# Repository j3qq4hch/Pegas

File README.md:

# Материнская плата БПЛА Pegas

Данный репозиторий содержит документацию и исходные файлы печатных плат электроники БПЛА Пегас.
Набортная электроника представляет собой главным образом материнскую плату (одну или набор из двух), которая служит для распределения питания внутри дрона, а также предоставляет интерфейс для подключения внешних устройств к автопилоту (удобные в производстве и использовании разъемы в удобных местах). БПЛА Пегас использует PX4-совместимый автопилот Cube Orange, которому всегда требуется некая материнская плата (carrier board в репозитории самого автопилота), т.к. он подключается ко всем внешним устройствам разъемом Hirose DF17(1.0H)-80DP-0.5V(57).

Было спроектировано несколько итераций электроники БПЛА Пегас.
## V1 
Самая первая версия устройства, состоящая из одной четырехслойной печатной платы.
Было произведен только один прототип, после чего была спроектирована следующая версия.

## V2
Минимальные отличия от V1, в частности: иная ориентация Cube Orange на плате (он повернут на 60 градусов), что было вызвано багом с устновлением нулевого положения встроенного компаса в ПО PX4, также добавлена схема выключения устройства на N-канальных полевых транзисторах. Схема выключения в этой версии неработоспособна и никогда не была исправлена. 

Также эта версия может быть дополнена внешним ethernet-роутером, который монтируется внутри фюзеляжа БПЛА на специальном кронштейне.

Было спроектировано две платы переходника для покупных модулей роутеров:

Было произведено несколько плат (до 10), которые используются в первых коммерческих аппаратах.

## V3
Полностью переработанная версия электроники: одна четырехслойная материнская плата  заменена на две двухслойные, соединенные мезонинным способом. Снизу располагается силовая плата, на которой размещаются разъемы для подключения моторов, медные полигоны распреления силового питания, DC-DC преобразователи всех вторичных линий питания, а также схема выключения на N-канальных полевых транзисторах. Сверху располагается плата логики с автопилотом и всеми разъемами для подключения внешних устройств. В этой версии произошел переход с миниатюрных разъемов серии JST-GH (как в UAVCAN) на несколько более крупные и значительно более удобные и надежные разъемы JST-XA с защелкой. 

Этот вариант материнской платы предназначен для сборки СЫЧ-версии Пегаса, поэтому помимо типичных компонентов на плате логики также располагается располагается покупной модуль ethernet-концентратора (ссылка тут) и модем телеметрии, поставляемый заказчиком (картинка тут).

Эта версия электроники никогда не была произведена и послужила основой для версии 3.1.

## V3.1

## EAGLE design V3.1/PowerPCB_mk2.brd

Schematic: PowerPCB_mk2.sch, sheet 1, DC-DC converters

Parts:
C1, C10, C16, C25, C39, C58: 0.1u; C0603; VOLTAGE 50V; LCSC# C14663
C2, C3, C4, C11, C12, C13, C17, C18, C19, C26, C27, C33, C44, C54: 2.2u; C1206; VOLTAGE 100V; LCSC# C170101
C5, C14, C20, C34, C45, C62, C88: 4700p; C0603; VOLTAGE 50V; LCSC# C106218
C6, C15, C21, C35, C87: 47p; C0603; VOLTAGE 50V; LCSC# C1671
C7, C8, C9, C22, C23, C24, C36, C37, C38, C43, C56, C57: 47u; C1206; VOLTAGE 25V; LCSC# C403725
C28, C29, C30, C31, C32, C42: 10u; C1210; VOLTAGE 50V; LCSC# C77102
C40, C41: DNP; C0603
CON1: PINHEAD_1X12-2.54-FEMALE; 1X12-PTH-2.54-FEMALE
CON2, CON4, CON7: PINHEAD_1X06-2.54-FEMALE; 1X06-PTH-2.54-FEMALE
CON3: PINHEAD_1X02-2.54-FEMALE; 1X02-PTH-2.54-FEMALE
D1, D2, D3, D4, D10: B560C; DO-214AB(SMC)
IC1, IC2, IC3, IC4: TPS54560B; SOIC8-POWERPAD
IC5: INA169; SOT23-5
IC10: TPS54260; MSOP10; DIGIKEY# 296-28183-1-ND
J1: CONNECTION-7MM; CONNECTION_7MM
L1: 3.3uH; IHLP-2020BZ-01; LCSC# C844988
L2, L4, L5: 7.2uH; 1064
L3: 22µH; SRP1265A
Q1: IRLML9301; SOT23
R1, R5, R9, R13: 243K; R0603; LCSC# C23351
R2, R6, R10, R14, R22, R29: 18K; R0603; LCSC# C25810
R3, R11: 53K6; R0603; LCSC# C23074
R4, R8, R12, R16, R17, R20, R23, R28: 10K; R0603; LCSC# C160601
R7, R15, R21, R25: 143K; R0603; LCSC# C22877
R18, R26: 700 µOhms; R3920-KELVIN
R27: 39K; R0603; LCSC# C23153
RL: 53K6; R0603; LCSC# C23074
RL1: DNM; R0603; LCSC# C23153

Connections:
5VFMU: C7.P$2 (2), C8.P$2 (2), C9.P$2 (2), C39.2, IC5.5 (V+), L2.2, Q1.2 (S), R3.2, R23.1; also elsewhere on the board
5V_FMU_CTRL: Q1.1 (G), R23.2
BATNEG: CON3.1
BATT_CURRENT: C40.2, CON1.12, IC5.1 (OUT), RL.2, RL1.2
BATT_VOLTAGE: C41.2, CON1.11, R20.2, R22.1
BOOT: C58.2, IC10.1 (BOOT)
BOOT1: C1.1, IC1.1 (BOOT)
BOOT2: C16.1, IC3.1 (BOOT)
BOOT3: C25.1, IC4.1 (BOOT)
DC-DC_EN: IC2.3 (EN), IC3.3 (EN), IC4.3 (EN), IC10.3 (EN); also elsewhere on the board
GND: C2.P$1 (1), C3.P$1 (1), C4.P$1 (1), C5.1, C6.1, C7.P$1 (1), C8.P$1 (1), C9.P$1 (1), C11.P$1 (1), C12.P$1 (1), C13.P$1 (1), C14.1, C15.1, C17.P$1 (1), C18.P$1 (1), C19.P$1 (1), C20.1, C21.1, C22.P$1 (1), C23.P$1 (1), C24.P$1 (1), C26.P$1 (1), C27.P$1 (1), C28.1, C29.1, C30.1, C31.1, C32.1, C33.P$1 (1), C34.1, C35.1, C36.P$1 (1), C37.P$1 (1), C38.P$1 (1), C39.1, C40.1, C41.1, C42.1, C43.P$2 (2), C44.P$1 (1), C45.2, C54.P$1 (1), C56.P$2 (2), C57.P$2 (2), C62.2, C87.2, C88.2, CON1.1, CON1.2, CON1.5, CON1.6, CON1.7, CON2.1, CON2.2, CON2.3, CON4.4, CON4.5, CON4.6, CON7.4, CON7.5, CON7.6, D1.A, D2.A, D3.A, D4.A, D10.A, IC1.7 (GND), IC1.P$1 (GND), IC2.7 (GND), IC2.P$1 (GND), IC3.7 (GND), IC3.P$1 (GND), IC4.7 (GND), IC4.P$1 (GND), IC5.2 (GND), IC10.9 (GND), IC10.EP (GND), J1.2, R1.1, R4.1, R5.1, R8.1, R9.1, R12.1, R13.1, R16.1, R17.1, R20.1, R25.1, R28.1, RL.1, RL1.1; also elsewhere on the board
unnamed: IC1.4 (RT/CLK), R1.2
unnamed: IC3.4 (RT/CLK), R9.2
unnamed: C6.2, IC1.6 (COMP), R2.2
unnamed: C5.2, R2.1
unnamed: IC1.5 (FB), R3.1, R4.2
unnamed: C21.2, IC3.6 (COMP), R10.2
unnamed: C10.1, IC2.1 (BOOT)
unnamed: C10.2, D2.C, IC2.8 (SW), L3.1
unnamed: IC2.4 (RT/CLK), R5.2
unnamed: C15.2, IC2.6 (COMP), R6.2
unnamed: C14.2, R6.1
unnamed: IC2.5 (FB), R7.1, R8.2, R17.2
unnamed: C20.2, R10.1
unnamed: IC4.4 (RT/CLK), R13.2
unnamed: IC3.5 (FB), R11.1, R12.2
unnamed: C35.2, IC4.6 (COMP), R14.2
unnamed: C34.2, R14.1
unnamed: IC4.5 (FB), R15.1, R16.2
unnamed: IC5.4 (VIN-), R18.S2, R26.S2
unnamed: C45.1, C62.1, IC10.4 (SS/TR)
unnamed: IC5.3 (VIN+), R18.S1, R26.S1
unnamed: R21.1, R22.2
unnamed: CON1.8, CON1.9, CON1.10, Q1.3 (D)
unnamed: C87.1, IC10.8 (COMP), R29.2
unnamed: IC10.5 (RT/CLK), R25.2
unnamed: C88.1, R29.1
PGND: J1.1; also elsewhere on the board
PH: C58.1, D10.C, IC10.10 (PH), L1.P$1 (1)
PWRSW: CON3.2
SW1: C1.2, D1.C, IC1.8 (SW), L2.1
SW2: C16.2, D3.C, IC3.8 (SW), L4.1
SW3: C25.2, D4.C, IC4.8 (SW), L5.1
VBAT: C2.P$2 (2), C3.P$2 (2), C4.P$2 (2), C11.P$2 (2), C12.P$2 (2), C13.P$2 (2), C17.P$2 (2), C18.P$2 (2), C19.P$2 (2), C26.P$2 (2), C27.P$2 (2), C33.P$2 (2), C44.P$2 (2), C54.P$2 (2), IC1.2 (VIN), IC2.2 (VIN), IC3.2 (VIN), IC4.2 (VIN), IC10.2 (VIN), R18.2, R18.22 (2), R21.2, R26.2, R26.22 (2); also elsewhere on the board
VDC: R18.1, R18.11 (1), R26.1, R26.11 (1); also elsewhere on the board
VDD_4V: C43.P$1 (1), C56.P$1 (1), C57.P$1 (1), CON1.3, CON1.4, L1.P$2 (2), R27.2
VDD_5V: C22.P$2 (2), C23.P$2 (2), C24.P$2 (2), CON4.1, CON4.2, CON4.3, L4.2, R11.2
VDD_12V: C36.P$2 (2), C37.P$2 (2), C38.P$2 (2), CON7.1, CON7.2, CON7.3, L5.2, R15.2
VDD_24V: C28.2, C29.2, C30.2, C31.2, C32.2, C42.2, CON2.4, CON2.5, CON2.6, L3.2, R7.2
VSENSE: IC10.7 (VSENSE), R27.1, R28.2

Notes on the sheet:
24V power source
5V power source
When EN is left floating TPS54560 is enabled
12V power source
EN - Enable terminal, with internal pull-up current source. Pull below 1.2 V to disable. Float to enable.
EN PIN: Pull below 1.2 V to disable. Float to enable.
143K on RT/CLK is for ~800 KHz switching frequency
TPS54560/54260 Vout = 0.8 * (Rh/Rl + 1)
Vout = 3,92 V
Vout = 23,68 V
Vout = 12,24 V
Vout = 5.088
Place C3 in case low pass filtering on the output needed
For most applications, best performance is attained with an RS value that provides a full-scale shunt voltage of 50 mV to 100 mV; maximum input voltage for accurate measurements is 500 mV.
Imax = 169 A Vout max = 3.17 V

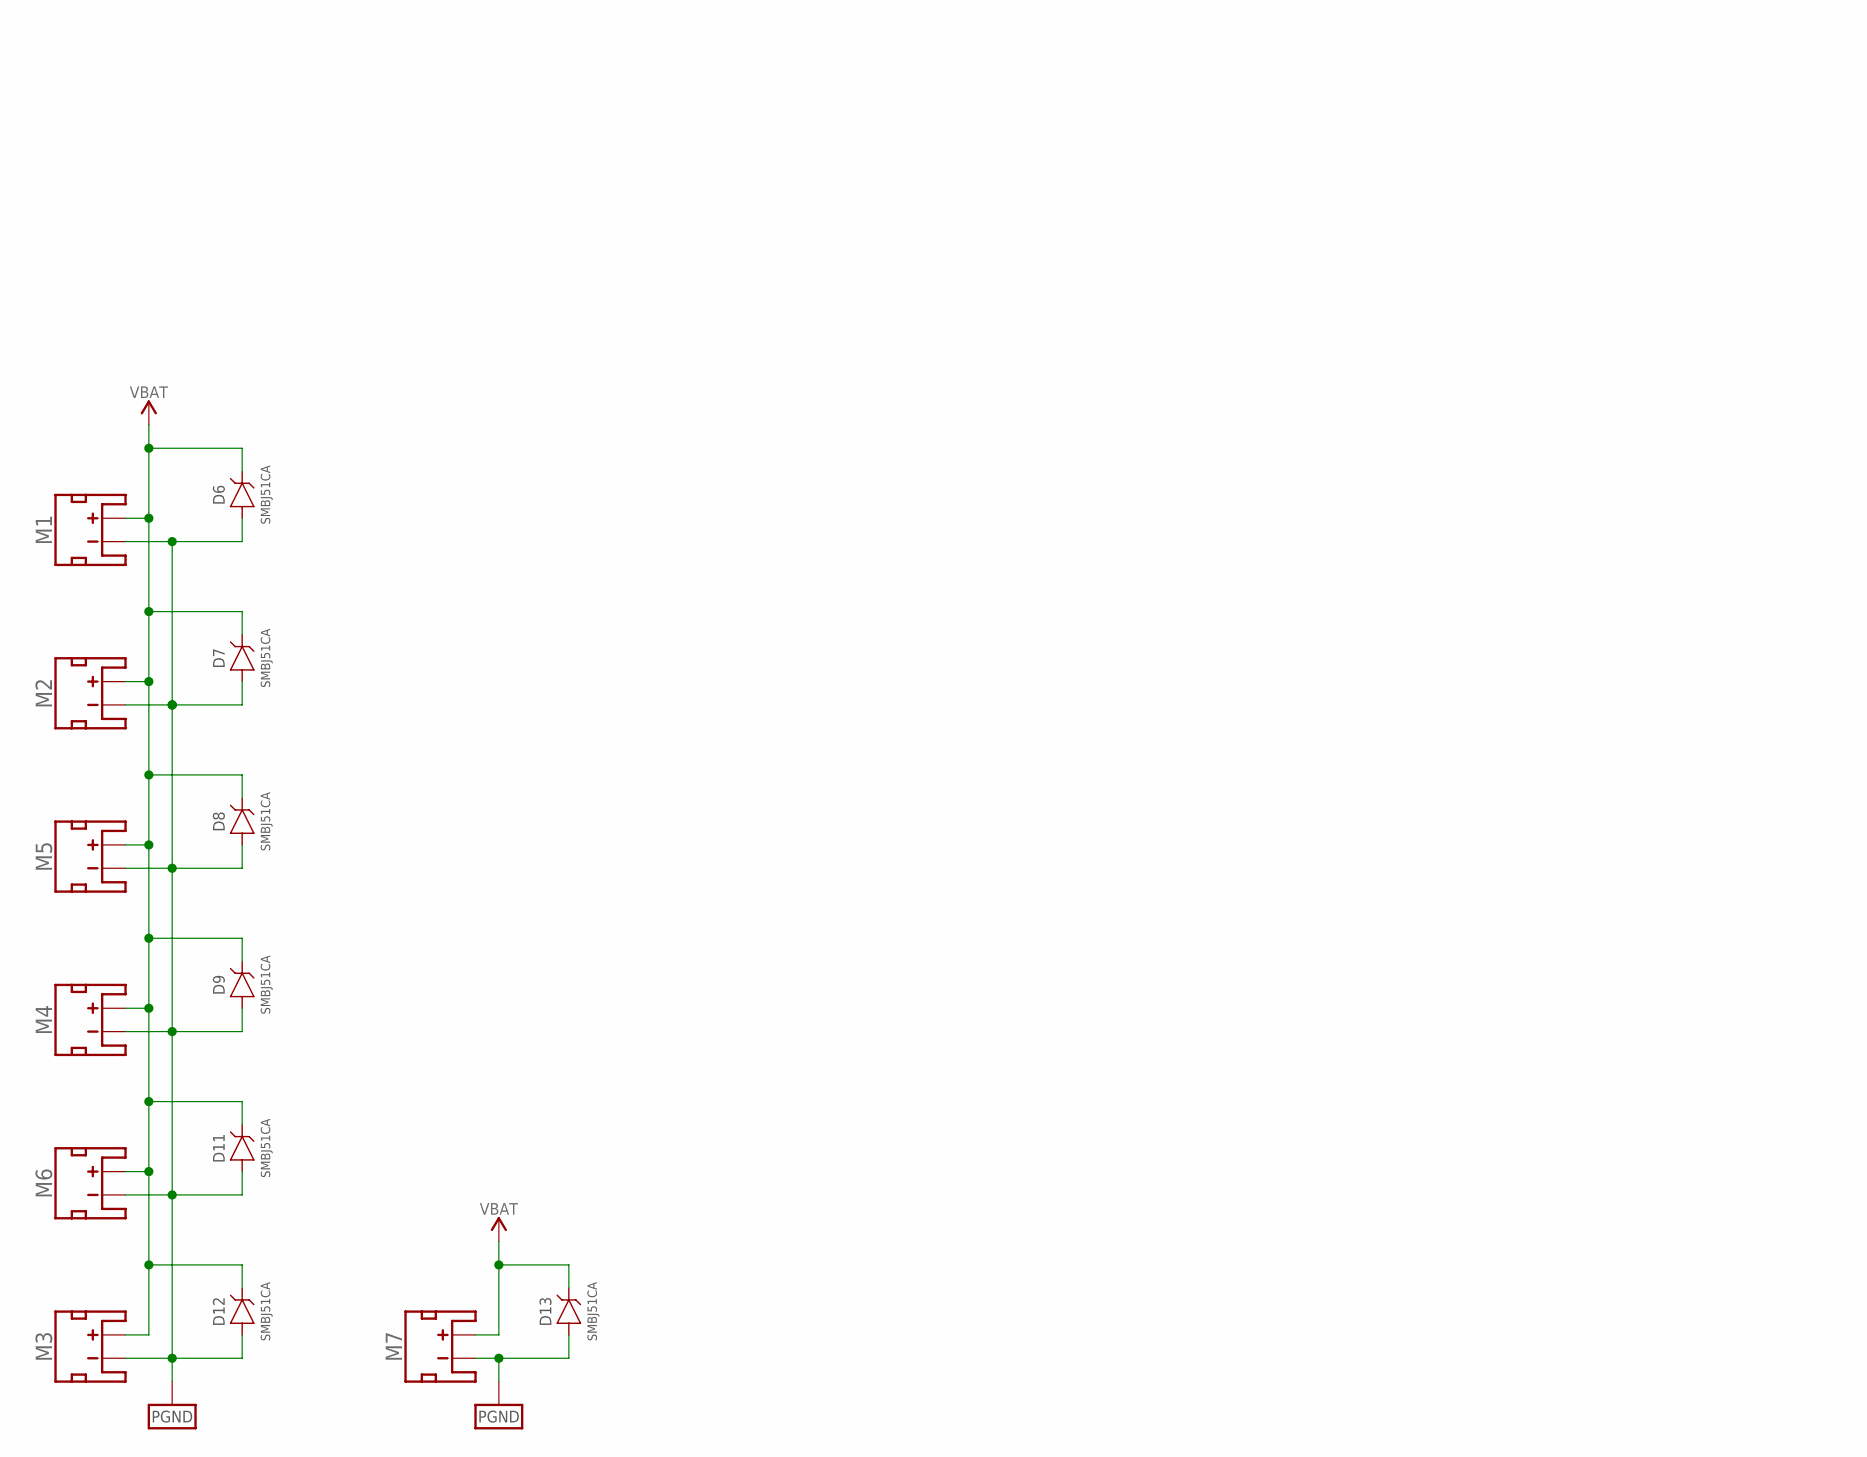
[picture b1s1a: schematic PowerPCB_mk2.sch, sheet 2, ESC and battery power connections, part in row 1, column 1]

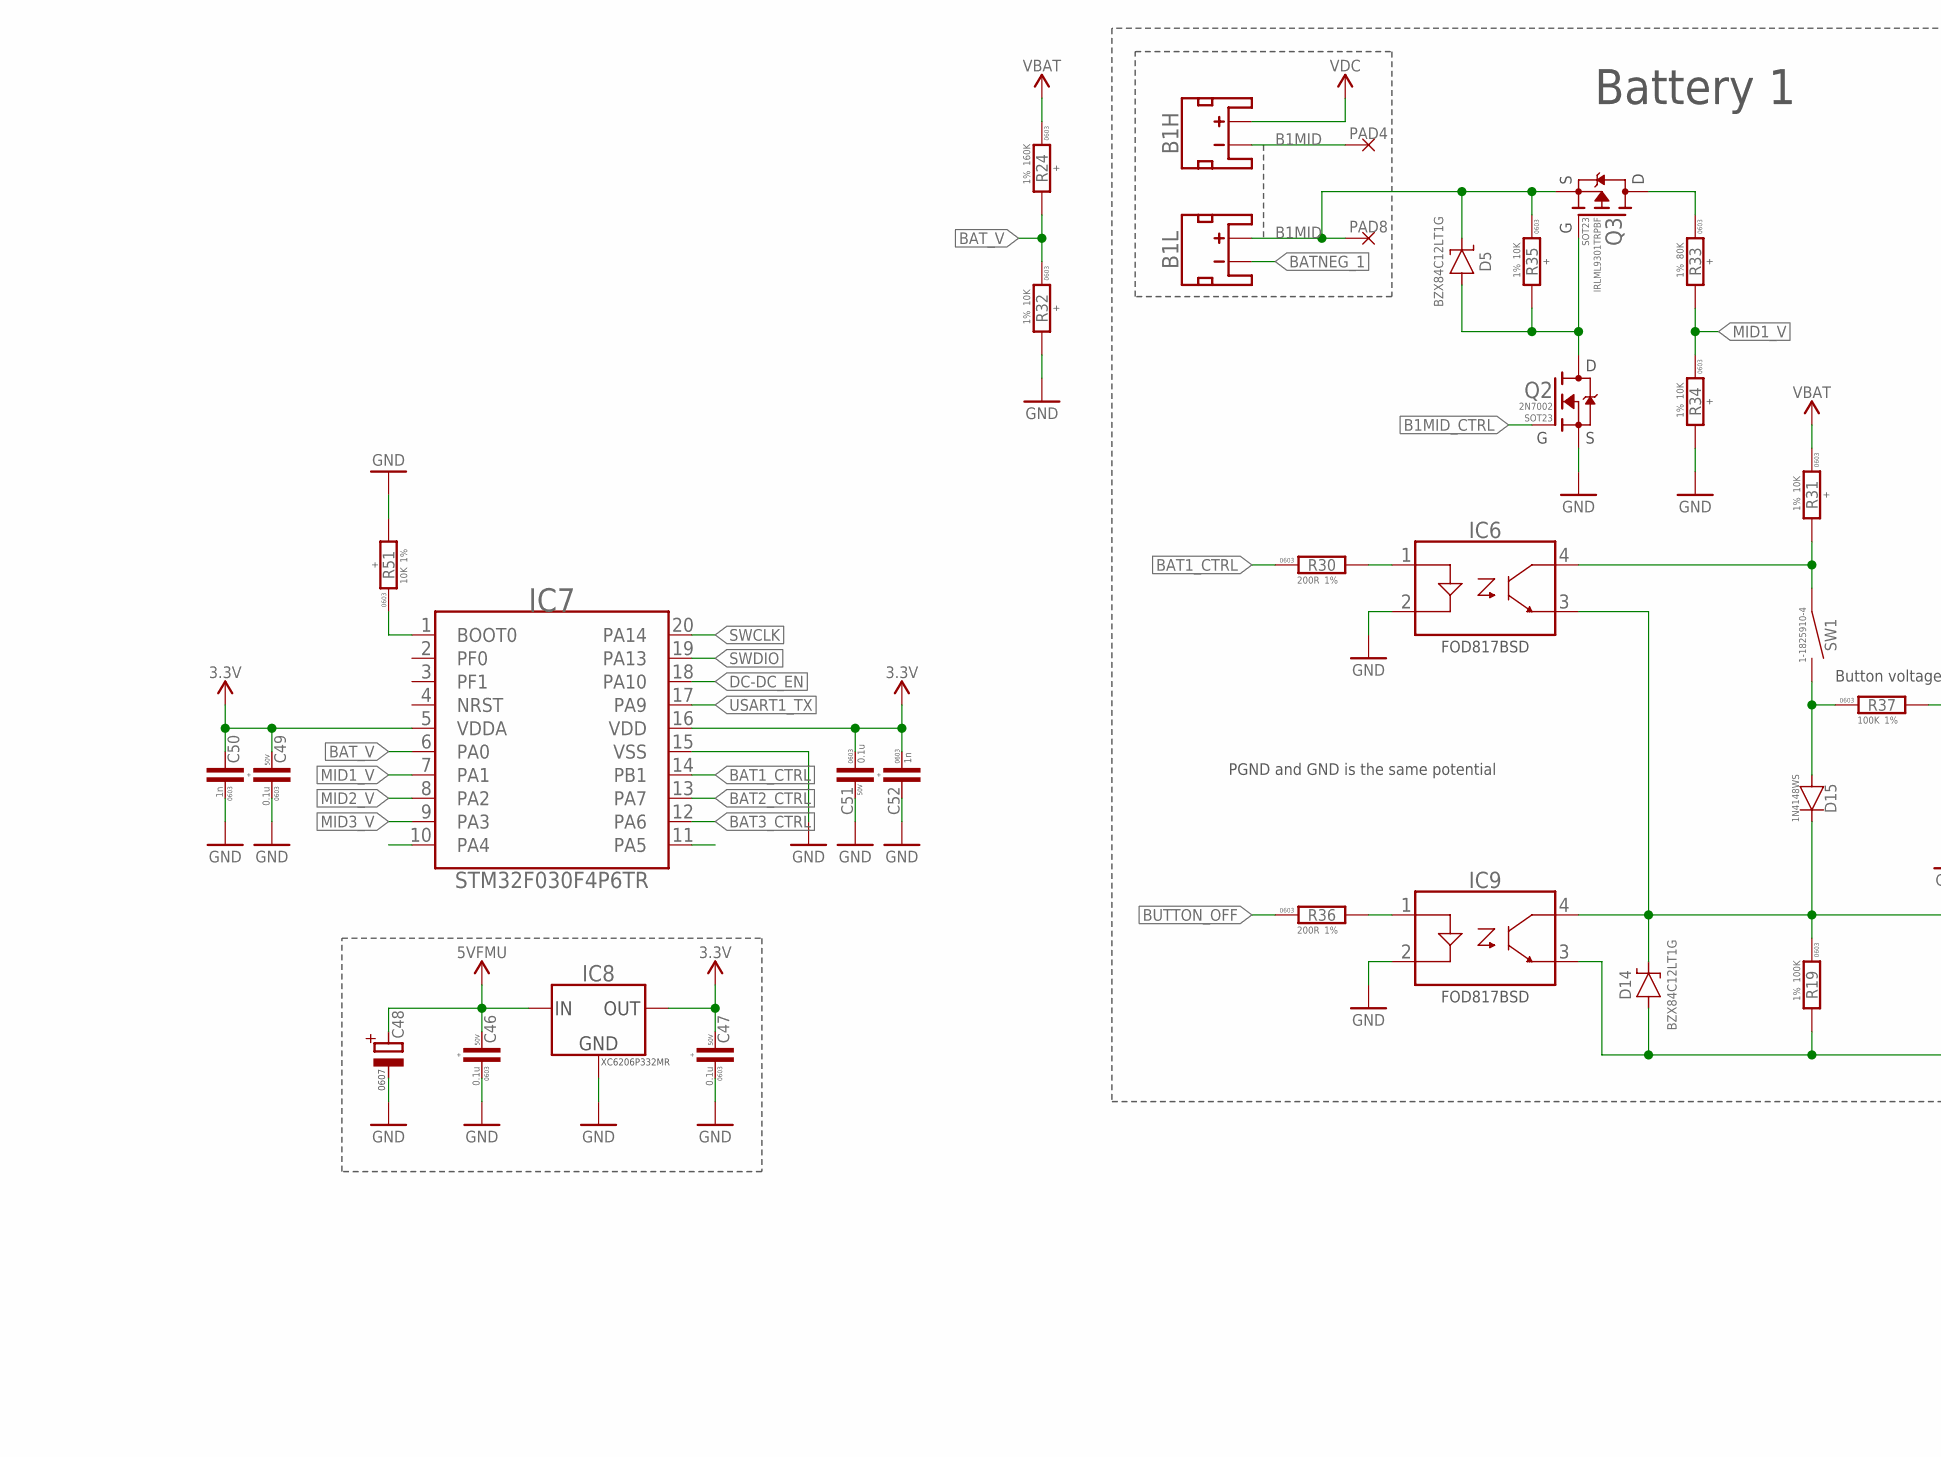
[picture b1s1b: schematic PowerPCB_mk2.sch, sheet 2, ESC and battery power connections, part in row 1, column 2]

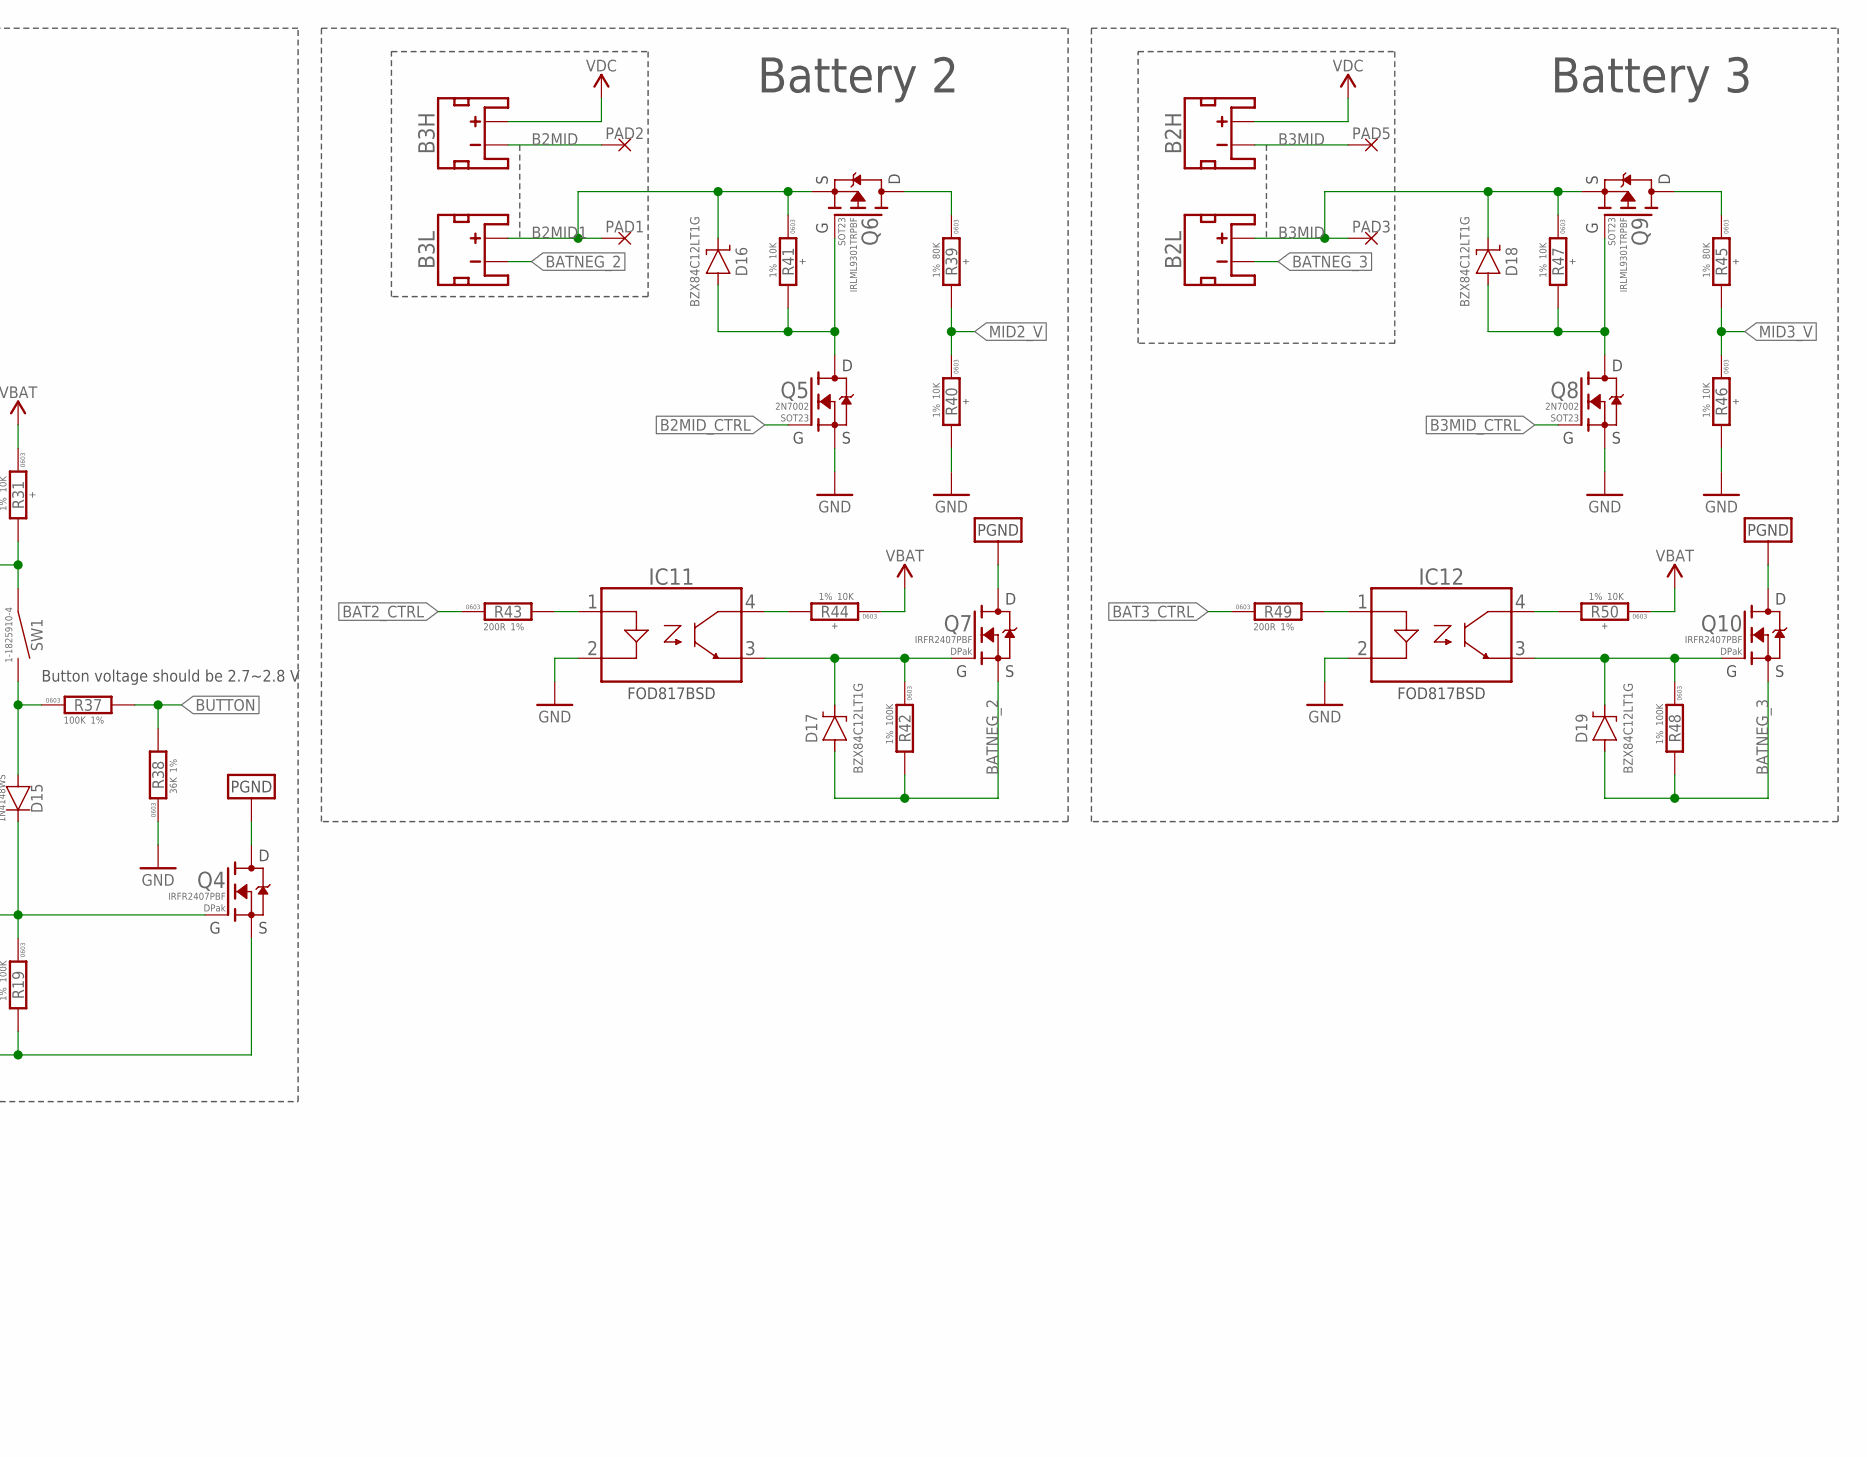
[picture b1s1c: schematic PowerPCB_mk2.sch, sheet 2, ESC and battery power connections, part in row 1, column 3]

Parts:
B1H, B1L, B2H, B2L, B3H, B3L: BATTERY_CON-XT60PW-M; XT60PW-M
C46, C47, C49, C51: 0.1u; C0603; VOLTAGE 50V; LCSC# C14663
C48: CPOL-SMD_6.3X7.7; CAP_SMD_6.3X7.7
C50, C52: 1n; C0603
D5, D14, D16, D17, D18, D19: BZX84C12; SOT23
D6, D7, D8, D9, D11, D12, D13: SMBJ51CA-SMB; DO-214AA(SMB)
D15: 1N4148WS; SOD323
IC6, IC9, IC11, IC12: FOD817; 4-SMD
IC7: STM32F030F4P6; TSSOP20
IC8: XC6206P332MR; SOT23
M1, M2, M3, M4, M5, M6, M7: BATTERY_CON-XT30-RA; XT30-RA
PAD1, PAD2, PAD3, PAD4, PAD5, PAD8: PAD-10X4; 10X4
Q2, Q5, Q8: 2N7002; SOT23
Q3, Q6, Q9: IRLML9301; SOT23
Q4, Q7, Q10: IRFR2407PBF; D-PAK
R19, R37, R42, R48: 100K; R0603
R24: 160K; R0603; LCSC# C160601
R30, R36, R43, R49: 200R; R0603
R31, R32, R34, R35, R40, R41, R44, R46, R47, R50, R51: 10K; R0603; LCSC# C160601
R33, R39, R45: 80K; R0603; LCSC# C160601
R38: 36K; R0603
SW1: TACT_SWITCH-1-1825910-4; 1-1825910-4

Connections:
5VFMU: C46.2, C48.+, IC8.3 (IN); also elsewhere on the board
B1MID: B1H.-, B1L.+, D5.3 (C), PAD4.P$1, PAD8.P$1, Q3.2 (S), R35.1
B1MID_CTRL: Q2.1 (G)
B2MID: B3H.-, PAD2.P$1
B2MID1: B3L.+, D16.3 (C), PAD1.P$1, Q6.2 (S), R41.1
B2MID_CTRL: Q5.1 (G)
B3MID: B2H.-, B2L.+, D18.3 (C), PAD3.P$1, PAD5.P$1, Q9.2 (S), R47.1
B3MID_CTRL: Q8.1 (G)
BAT1_CTRL: IC7.14 (PB1), R30.1
BAT2_CTRL: IC7.13 (PA7), R43.1
BAT3_CTRL: IC7.12 (PA6), R49.1
BATNEG_1: B1L.-, D14.1 (A), IC9.3 (EMITTER), Q4.S, R19.2
BATNEG_2: B3L.-, D17.1 (A), Q7.S, R42.2
BATNEG_3: B2L.-, D19.1 (A), Q10.S, R48.2
BAT_V: IC7.6 (PA0), R24.2, R32.1
BUTTON: R37.2, R38.2
BUTTON_OFF: R36.1
DC-DC_EN: IC7.18 (PA10); also elsewhere on the board
GND: C46.1, C47.1, C48.-, C49.1, C50.1, C51.2, C52.2, IC6.2 (C), IC7.15 (VSS), IC8.1 (GND), IC9.2 (C), IC11.2 (C), IC12.2 (C), Q2.2 (S), Q5.2 (S), Q8.2 (S), R32.2, R34.2, R38.1, R40.2, R46.2, R51.2; also elsewhere on the board
MID1_V: IC7.7 (PA1), R33.2, R34.1
MID2_V: IC7.8 (PA2), R39.2, R40.1
MID3_V: IC7.9 (PA3), R45.2, R46.1
unnamed: D14.3 (C), D15.C, IC6.3 (EMITTER), IC9.4 (COLLECTOR), Q4.G, R19.1
unnamed: IC6.1 (A), R30.2
unnamed: IC6.4 (COLLECTOR), R31.2, SW1.1, SW1.2 (1)
unnamed: IC9.1 (A), R36.2
unnamed: D15.A, R37.1, SW1.3 (2), SW1.4 (2)
unnamed: D5.1 (A), Q2.3 (D), Q3.1 (G), R35.2
unnamed: Q3.3 (D), R33.1
unnamed: Q6.3 (D), R39.1
unnamed: D16.1 (A), Q5.3 (D), Q6.1 (G), R41.2
unnamed: IC11.1 (A), R43.2
unnamed: D17.3 (C), IC11.3 (EMITTER), Q7.G, R42.1
unnamed: Q9.3 (D), R45.1
unnamed: IC11.4 (COLLECTOR), R44.2
unnamed: D18.1 (A), Q8.3 (D), Q9.1 (G), R47.2
unnamed: IC12.1 (A), R49.2
unnamed: D19.3 (C), IC12.3 (EMITTER), Q10.G, R48.1
unnamed: IC12.4 (COLLECTOR), R50.2
unnamed: IC7.1 (BOOT0), R51.1
PGND: D6.A, D7.A, D8.A, D9.A, D11.A, D12.A, D13.A, M1.-, M2.-, M3.-, M4.-, M5.-, M6.-, M7.-, Q4.D, Q7.D, Q10.D; also elsewhere on the board
SWCLK: IC7.20 (PA14)
SWDIO: IC7.19 (PA13)
USART1_TX: IC7.17 (PA9)
VBAT: D6.C, D7.C, D8.C, D9.C, D11.C, D12.C, D13.C, M1.+, M2.+, M3.+, M4.+, M5.+, M6.+, M7.+, R24.1, R31.1, R44.1, R50.1; also elsewhere on the board
VDC: B1H.+, B2H.+, B3H.+; also elsewhere on the board
VDD_3V3: C47.2, C49.2, C50.2, C51.1, C52.1, IC7.5 (VDDA), IC7.16 (VDD), IC8.2 (OUT)

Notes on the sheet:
Battery 1
Battery 2
Button voltage should be 2.7~2.8 V
PGND and GND is the same potential
Battery 3

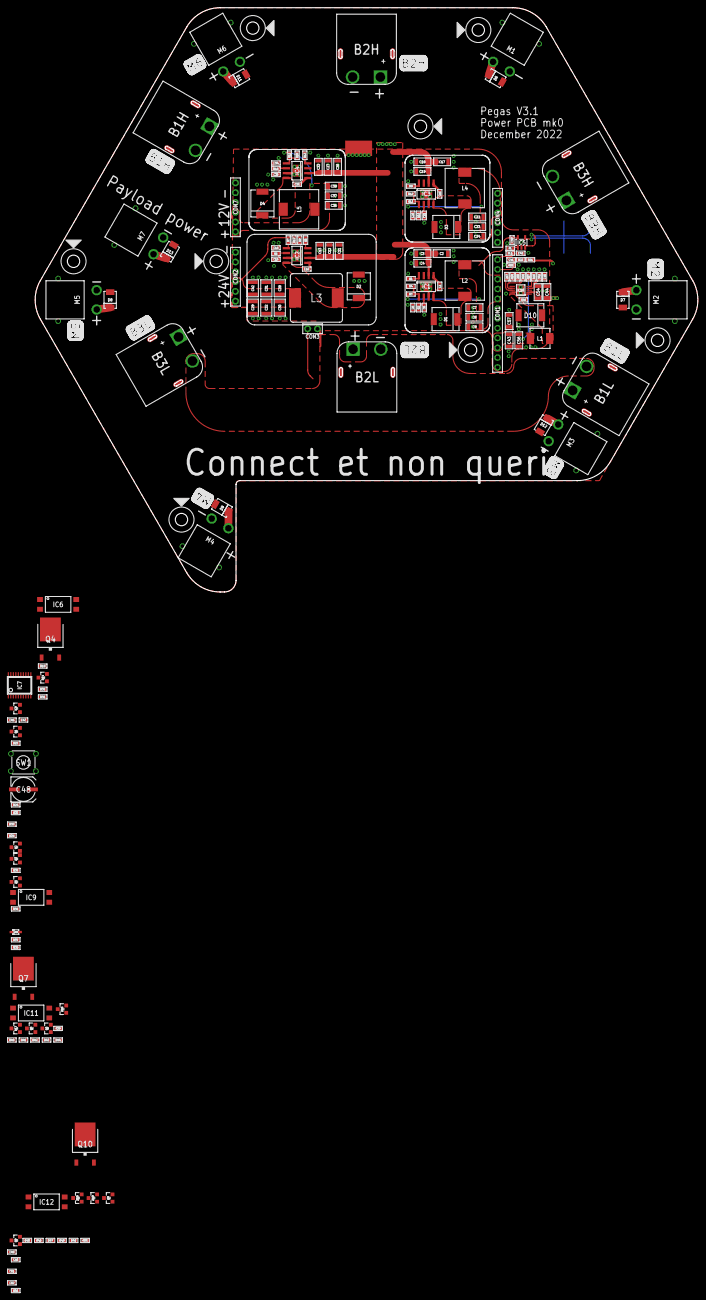
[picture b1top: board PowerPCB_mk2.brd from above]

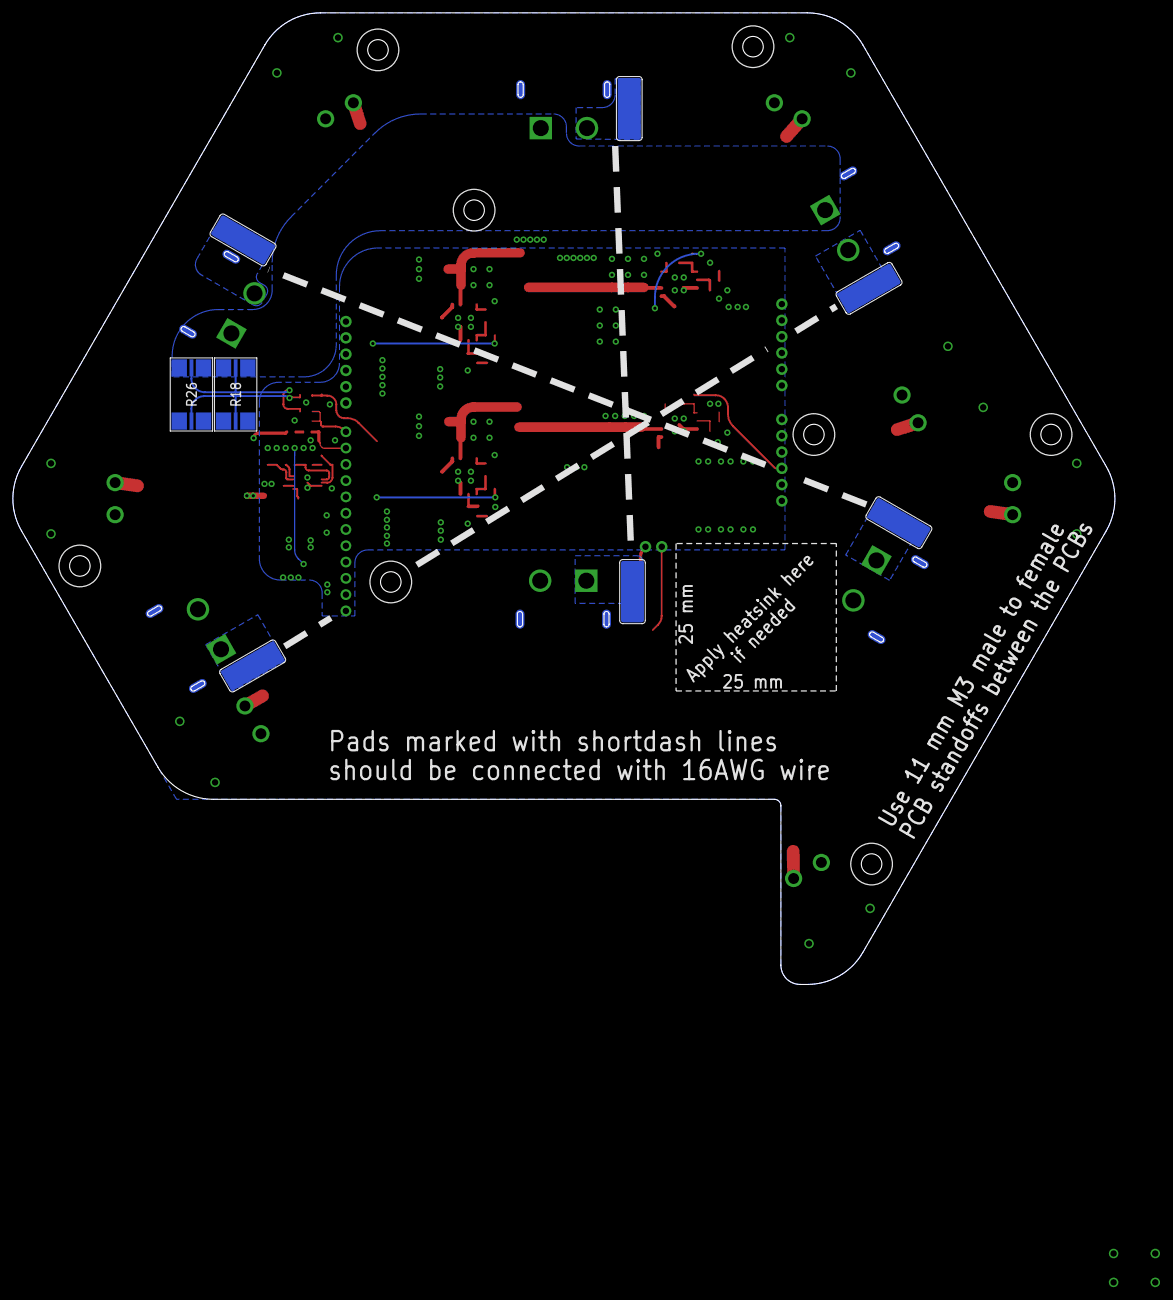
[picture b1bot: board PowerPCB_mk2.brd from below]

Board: 2 copper layers, 171.9 x 151.6 mm, 184 parts (8 on the bottom side), 82 nets.
